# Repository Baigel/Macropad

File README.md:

This project is modified from Mattia Dal Ben's YamPad with a few changes that suit my specific needs (credit: https://github.com/mattdibi/yampad)

The Yampad project is an open-source, [QMK (Quantum Mechanical Keyboard Firmware)](https://github.com/qmk/qmk_firmware) powered, hot-swappable, RGB-backlighted, OLED featured, mechanical numpad.

## Primary Modifications from Original YamPad
 - Added 2 more switches for an array of 4x5 buttons (no more 2u keys)
 - Added spot for an IR sensor
 - Made the unused pins more accessible (added them as expansion pins on the side; with room for a decoupling capacitor)
 - Redid the PCB design (basically designed the PCB from scratch, used Mattia Dal Ben's design as a guide)
 - Different mounting holes (in hindsight, the Pro Micro may cover the holes in the top right - Oops!)

## YamPad Features:
- Cheap to build: the PCB can be manufactured for less than 1$ per piece.
- Easy to source components.
- Easy to build.
- Hot swappable keys using *Kailh PCB sockets*.
- Arduino Pro Micro powered.
- QMK compatible.
- RGB backlighting support (optional).
- OLED 0.91" screen (optional).
- Completely open-source.

## Bill of materials

| Qty | Item                                 | Notes                                     |
|-----|--------------------------------------|-------------------------------------------|
| 1   | Arduino Pro Micro (ATmega32u4)       | a.k.a. SparkFun Pro Micro                 |
| 20  | Cherry MX compatible switches        |                                           |
| 20  | SOD-123 1N4148/1N4148W diodes        |                                           |
| 20  | Kailh PCB sockets CPG151101S11       |                                           |
| 10  | WS2812B RGB LEDs                     |                                           |
| 10  | SMD 0805 100nF capacitors            |                                           |
| 1   | I2C 0.91" 128*32 OLED Display Module | The ones using SSD1306 driver IC over I2C |
| 1   | 6mm*6mm button switch                |                                           |
| 1   | YamPAD/Macropad PCB                  |                                           |
| 5   | M3 screws                            |                                           |

Note that I have included my personal shopping list (with links) in /Macropad/Bill_of_Materials.txt for reference

## Assembly guide

Not necessary to assemble in this order. More details can be found on the official YamPad repository (https://github.com/mattdibi/yampad).

1. Start with soldering the **WS2812 LEDs**. Start by applying solder to a pad, then heat it up while adding the component, finally solder the remaining pads.
2. Now add the **0805 100nF caps**. Use the same technique as before.
3. Add the **1N4148 diodes**.
4. Add the **CPG151101S11 Kailh PCB sockets**.
5. Add the **reset 6mm button switch**.
6. Add some electrical tape just to be sure.
7. Add the **Arduino Pro Micro** bottom side up.
8. Add the **OLED screen**
9. Move to the firmware section and you should be set!

## Firmware

For now the firmware is available through mattdibi's [QMK firmware repository fork](https://github.com/mattdibi/qmk_firmware/tree/yampad).

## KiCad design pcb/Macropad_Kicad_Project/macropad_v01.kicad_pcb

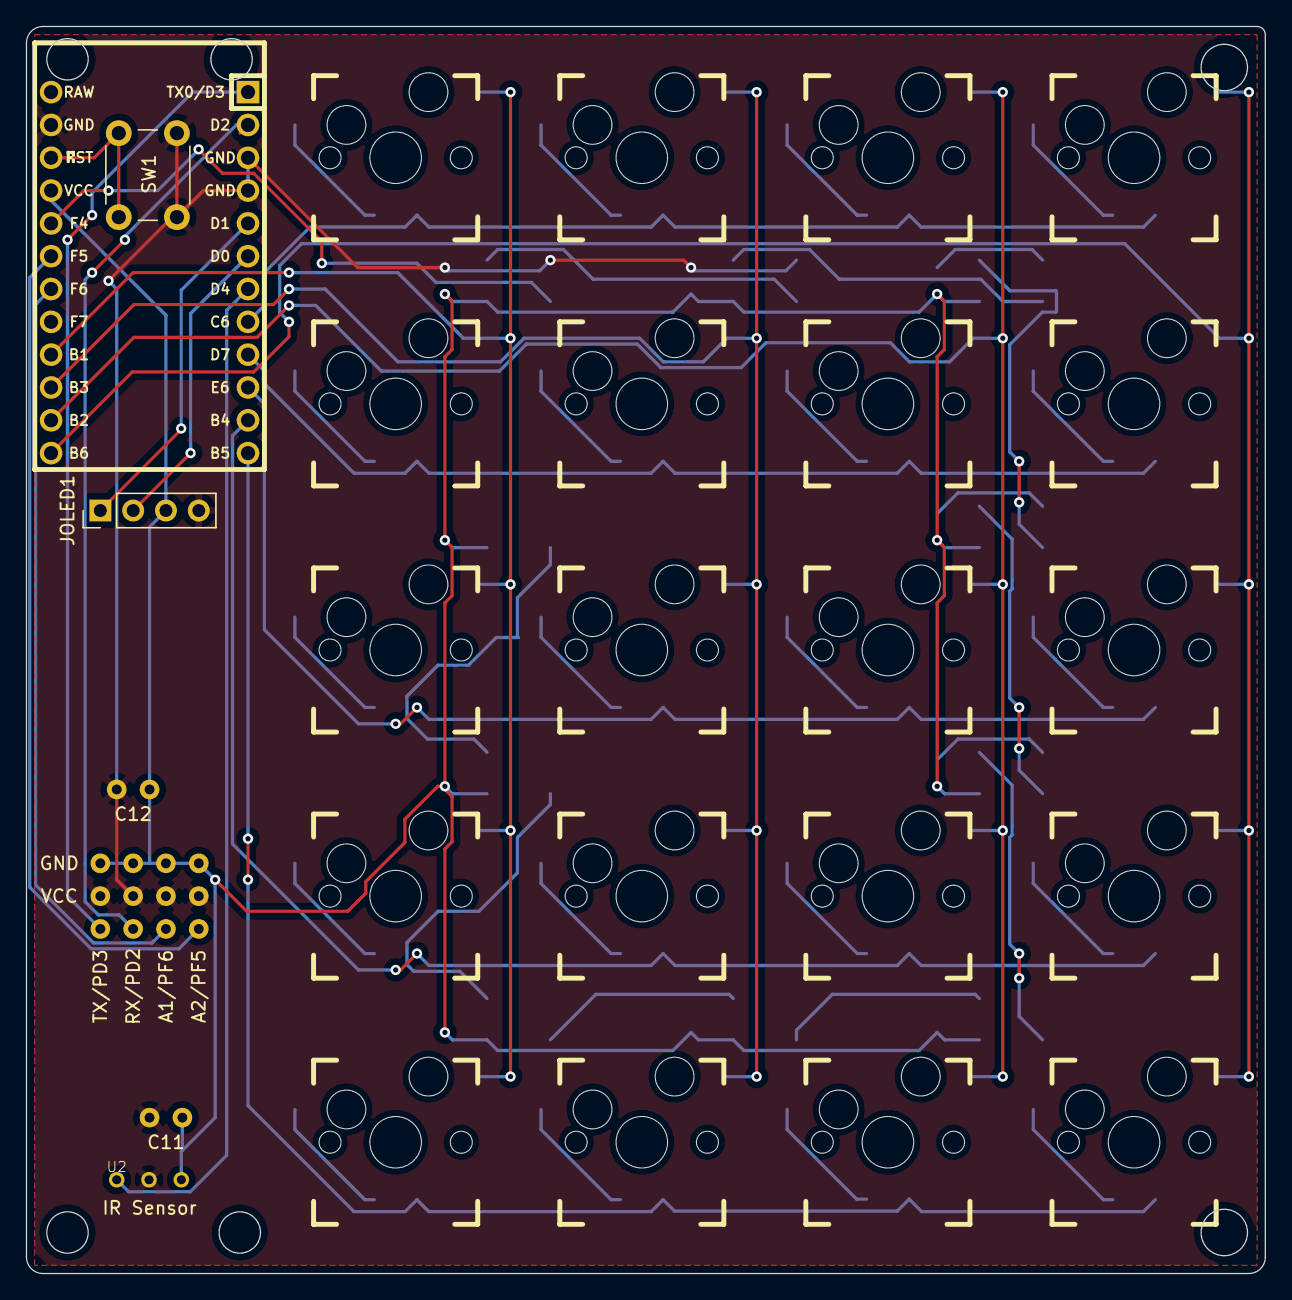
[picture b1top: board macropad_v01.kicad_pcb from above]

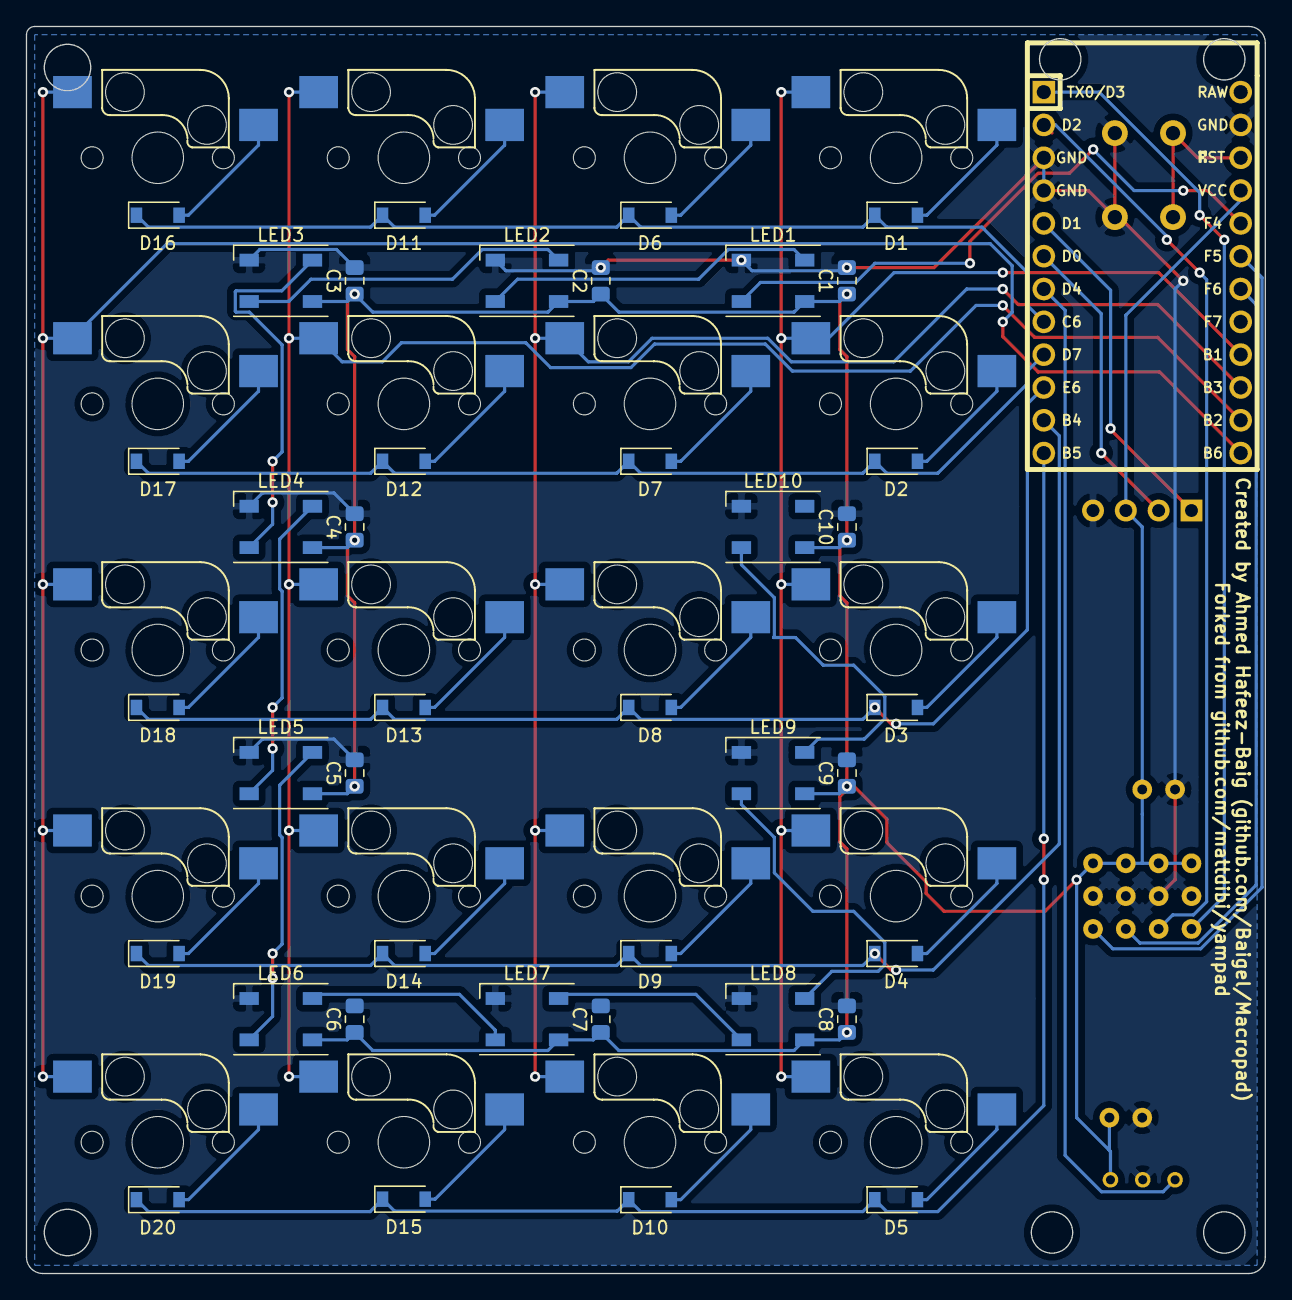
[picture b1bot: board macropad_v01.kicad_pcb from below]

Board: 2 copper layers, 95.9 x 96.5 mm, 67 parts (41 on the bottom side), 49 nets.

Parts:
C1, C2, C3, C4, C5, C6, C7, C8, C9, C10: 104; C_0805_2012Metric_Pad1.15x1.40mm_HandSolder
C11: macropad_v01-rescue_Symbols-Cache_Device_C-Symbol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; Capacitor-(100uF)
C12: Device_C-Symbols-Cache; Capacitor-(100uF)
D1, D2, D3, D4, D5, D6, D7, D8, D9, D10, D11, D12, D13, D14, D15, D16, D17, D18, D19, D20: D; D_SOD-123
J2: Expansion-Connector; Expansion-Pins
JOLED1: Conn_01x04; PinHeader_1x04_P2.54mm_Vertical
K1, K2, K3, K4, K5, K6, K7, K8, K9, K10, K11, K12, K13, K14, K15, K18, K19, K20: KEYSW; Kailh-PCB-Socket-1U-Cutout
K16, K17: KEYSW-canadian_parts-yampad_v2-rescue; Kailh-PCB-Socket-1U-Cutout
LED1, LED2, LED3, LED4, LED5, LED6, LED7, LED8, LED9, LED10: WS2812B; LED_WS2812B_PLCC4_5.0x5.0mm_P3.2mm
SW1: SW_Push; SW_PUSH_6mm
U1: ProMicro; ArduinoProMicro
U2: IR-Sensor; TSOP-382

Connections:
A1: J2.3, U1.18
A2: J2.4, U1.19
COL0: K1.1, K2.1, K3.1, K4.1, K5.1, U1.16
COL1: K6.1, K7.1, K8.1, K9.1, K10.1, U1.15
COL2: K11.1, K12.1, K13.1, K14.1, K15.1, U1.14
COL3: K16.1, K17.1, K18.1, K19.1, K20.1, U1.13
GND: C1.1, C2.1, C3.1, C4.1, C5.1, C6.1, C7.1, C8.1, C9.1, C10.1, C11.1, C12.1, J2.5, J2.6, J2.7, J2.8, JOLED1.4, LED1.3, LED2.3, LED3.3, LED4.3, LED5.3, LED6.3, LED7.3, LED8.3, LED9.3, LED10.3, SW1.1, U1.3, U1.4, U1.23, U2.GND
IR: U1.7, U2.OUT
LEDs: LED1.4, U1.20
unnamed: D1.2, K1.2
unnamed: D2.2, K2.2
unnamed: D3.2, K3.2
unnamed: D4.2, K4.2
unnamed: D5.2, K5.2
unnamed: D6.2, K6.2
unnamed: D7.2, K7.2
unnamed: D8.2, K8.2
unnamed: D9.2, K9.2
unnamed: D10.2, K10.2
unnamed: D11.2, K11.2
unnamed: D12.2, K12.2
unnamed: D13.2, K13.2
unnamed: D14.2, K14.2
unnamed: D15.2, K15.2
unnamed: D16.2, K16.2
unnamed: D17.2, K17.2
unnamed: D18.2, K18.2
unnamed: D19.2, K19.2
unnamed: D20.2, K20.2
unnamed: LED1.2, LED2.4
unnamed: LED2.2, LED3.4
unnamed: LED3.2, LED4.4
unnamed: LED4.2, LED5.4
unnamed: LED5.2, LED6.4
unnamed: LED6.2, LED7.4
unnamed: LED7.2, LED8.4
unnamed: LED8.2, LED9.4
unnamed: LED9.2, LED10.4
ROW0: D1.1, D6.1, D11.1, D16.1, U1.8
ROW1: D2.1, D7.1, D12.1, D17.1, U1.9
ROW2: D3.1, D8.1, D13.1, D18.1, U1.10
ROW3: D4.1, D9.1, D14.1, D19.1, U1.11
ROW4: D5.1, D10.1, D15.1, D20.1, U1.12
RST: SW1.2, U1.22
RX: J2.2, U1.2
SCL: JOLED1.2, U1.6
SDA: JOLED1.1, U1.5
TX: J2.1, U1.1
VCC: C1.2, C2.2, C3.2, C4.2, C5.2, C6.2, C7.2, C8.2, C9.2, C10.2, C11.2, C12.2, J2.9, J2.10, J2.11, J2.12, JOLED1.3, LED1.1, LED2.1, LED3.1, LED4.1, LED5.1, LED6.1, LED7.1, LED8.1, LED9.1, LED10.1, U1.21, U2.VS

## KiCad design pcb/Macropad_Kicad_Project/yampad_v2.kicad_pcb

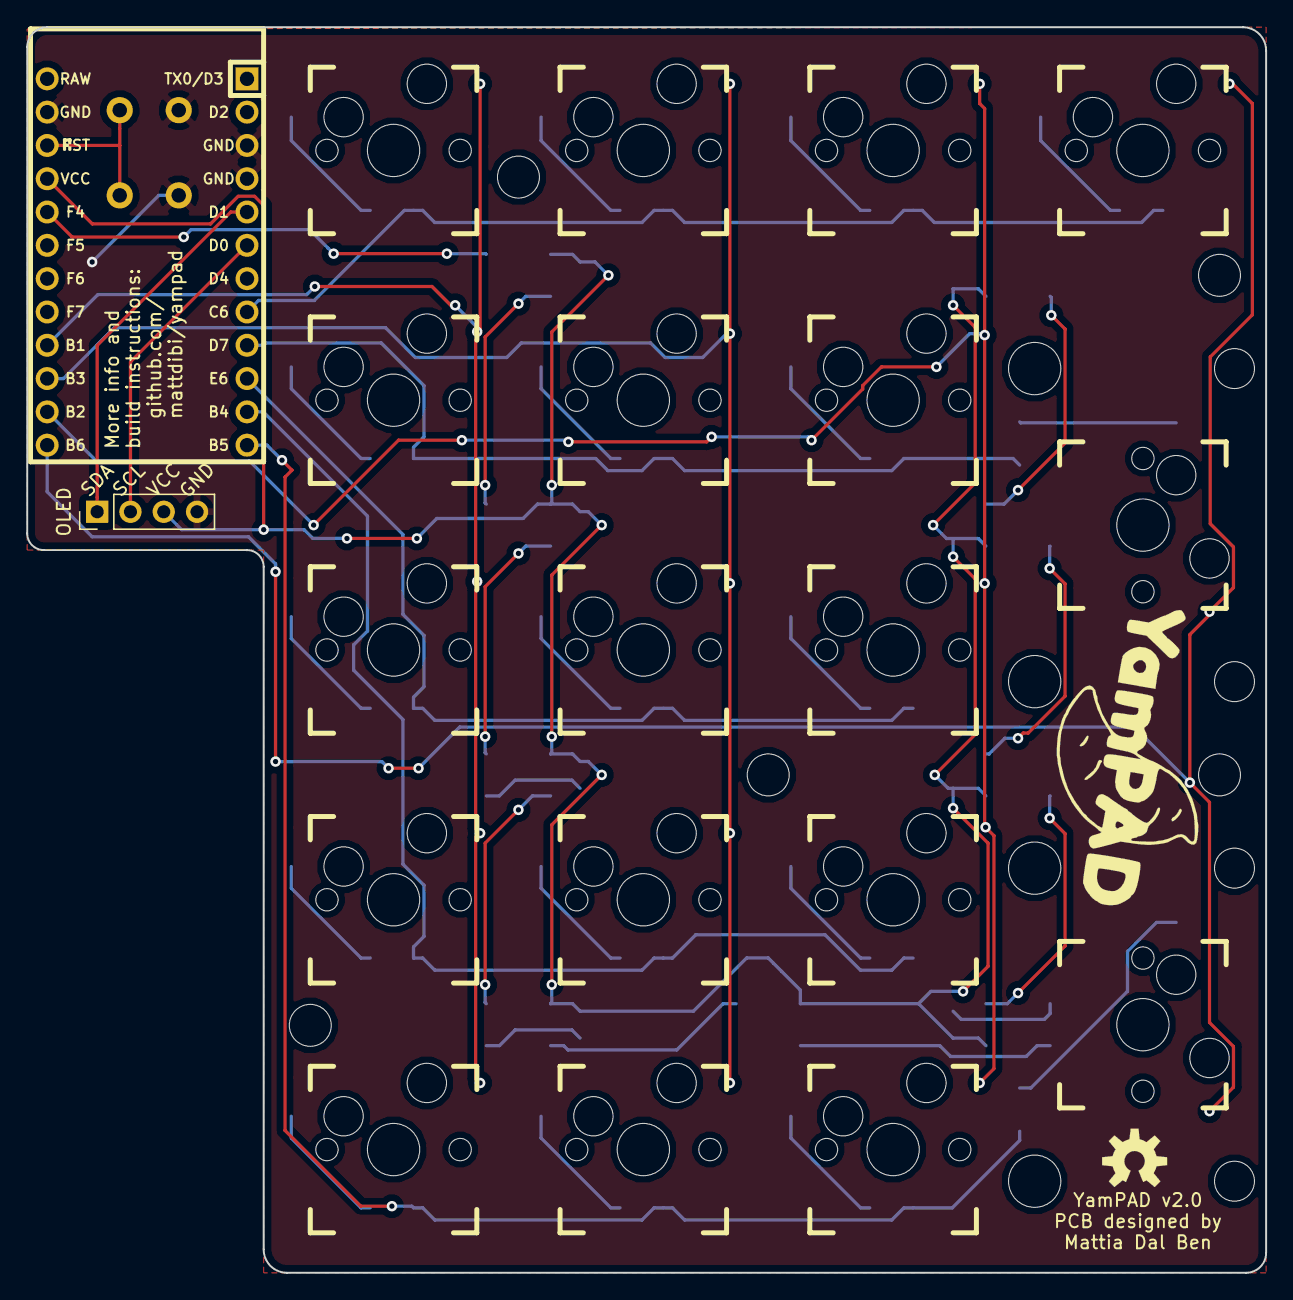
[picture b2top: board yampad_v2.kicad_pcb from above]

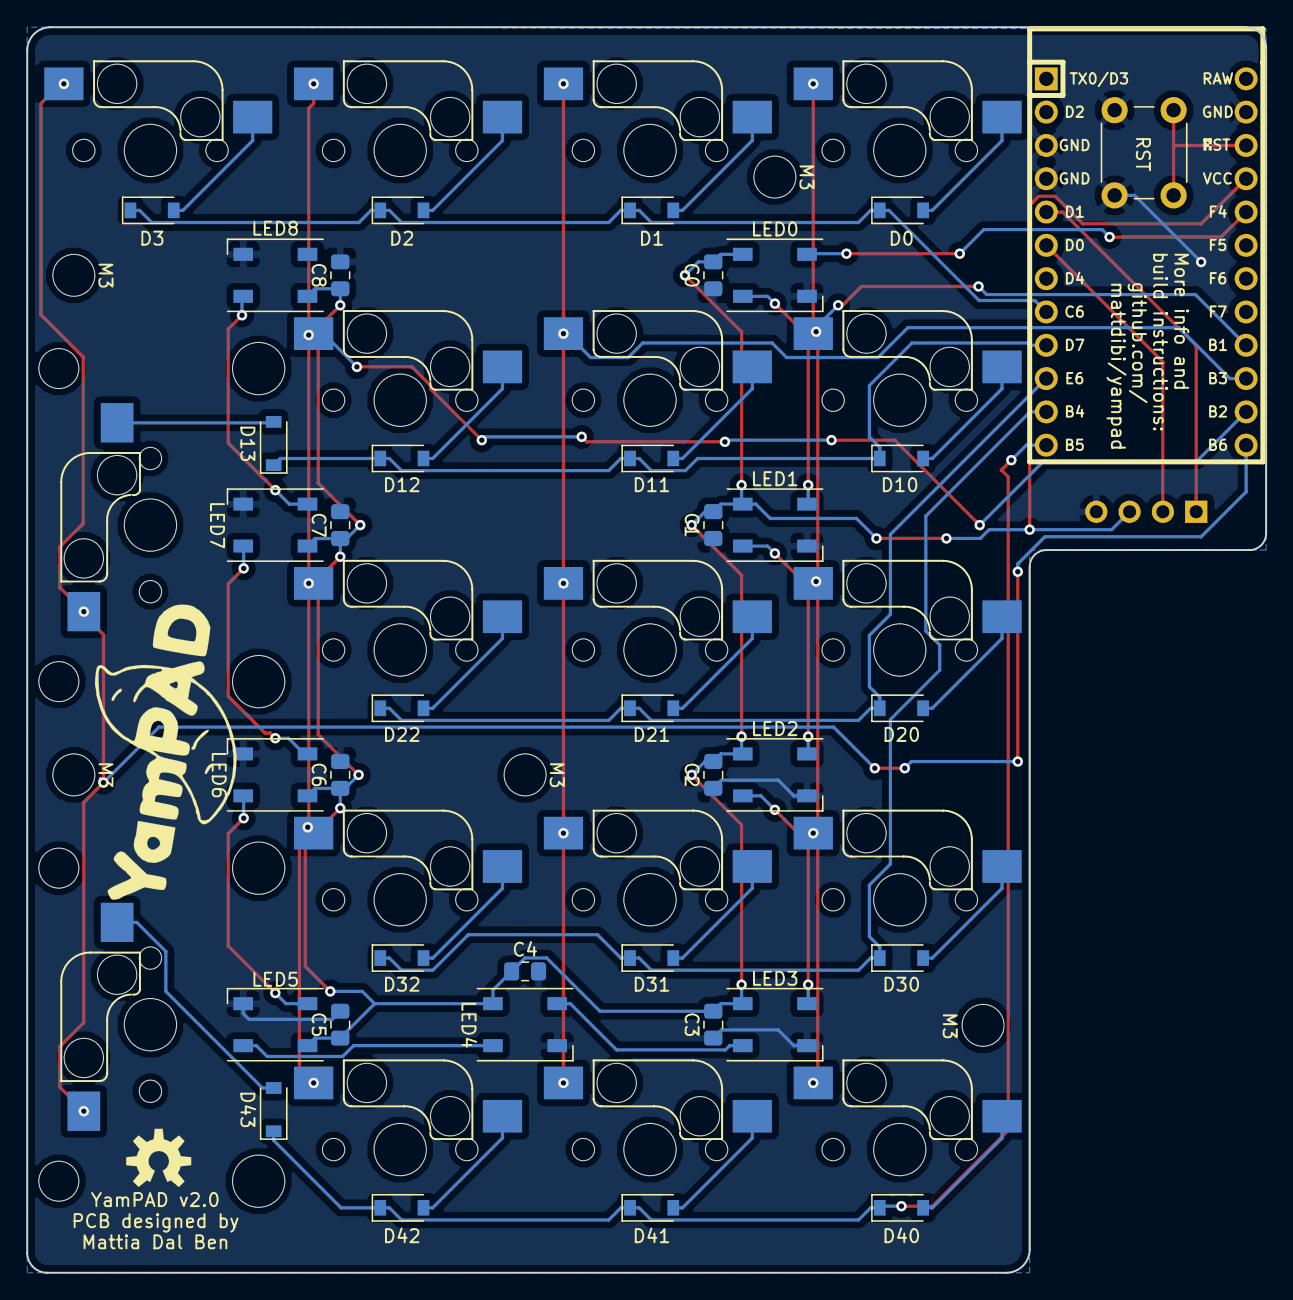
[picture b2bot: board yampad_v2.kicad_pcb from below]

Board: 2 copper layers, 94.5 x 95.0 mm, 62 parts (43 on the bottom side), 41 nets.

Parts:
C0, C1, C2, C3, C4, C5, C6, C7, C8: 104; C_0805_2012Metric_Pad1.15x1.40mm_HandSolder
D0, D1, D2, D3, D10, D11, D12, D13, D20, D21, D22, D30, D31, D32, D40, D41, D42, D43: D; D_SOD-123
K0, K1, K2, K3, K10, K11, K12, K20, K21, K22, K30, K31, K32, K40, K41, K42: KEYSW; Kailh-PCB-Socket-1U-Cutout
K13, K43: KEYSW; Kailh-PCB-Socket-2U
LED0, LED1, LED2, LED3, LED4, LED5, LED6, LED7, LED8: WS2812B; LED_WS2812B_PLCC4_5.0x5.0mm_P3.2mm
M3, M3#2, M3#3, M3#4, M3#5: MountingHole_3.2mm_M3
OLED: Conn_01x04; PinHeader_1x04_P2.54mm_Vertical
RST: SW_Push; SW_PUSH_6mm
U0: ProMicro; ArduinoProMicro

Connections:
COL0: K0.1, K10.1, K20.1, K30.1, K40.1, U0.16
COL1: K1.1, K11.1, K21.1, K31.1, K41.1, U0.15
COL2: K2.1, K12.1, K22.1, K32.1, K42.1, U0.14
COL3: K3.1, K13.1, K43.1, U0.13
GND: C0.1, C1.1, C2.1, C3.1, C4.1, C5.1, C6.1, C7.1, C8.1, LED0.3, LED1.3, LED2.3, LED3.3, LED4.3, LED5.3, LED6.3, LED7.3, LED8.3, OLED.4, RST.1, U0.3, U0.4, U0.23
LEDs: LED0.4, U0.20
unnamed: D0.2, K0.2
unnamed: D1.2, K1.2
unnamed: D2.2, K2.2
unnamed: D3.2, K3.2
unnamed: D10.2, K10.2
unnamed: D11.2, K11.2
unnamed: D12.2, K12.2
unnamed: D13.2, K13.2
unnamed: D20.2, K20.2
unnamed: D21.2, K21.2
unnamed: D22.2, K22.2
unnamed: D30.2, K30.2
unnamed: D31.2, K31.2
unnamed: D32.2, K32.2
unnamed: D40.2, K40.2
unnamed: D41.2, K41.2
unnamed: D42.2, K42.2
unnamed: D43.2, K43.2
unnamed: LED0.2, LED1.4
unnamed: LED1.2, LED2.4
unnamed: LED2.2, LED3.4
unnamed: LED3.2, LED4.4
unnamed: LED4.2, LED5.4
unnamed: LED5.2, LED6.4
unnamed: LED6.2, LED7.4
unnamed: LED7.2, LED8.4
ROW0: D0.1, D1.1, D2.1, D3.1, U0.8
ROW1: D10.1, D11.1, D12.1, D13.1, U0.9
ROW2: D20.1, D21.1, D22.1, U0.10
ROW3: D30.1, D31.1, D32.1, U0.11
ROW4: D40.1, D41.1, D42.1, D43.1, U0.12
RST: RST.2, U0.22
SCL: OLED.2, U0.6
SDA: OLED.1, U0.5
VCC: C0.2, C1.2, C2.2, C3.2, C4.2, C5.2, C6.2, C7.2, C8.2, LED0.1, LED1.1, LED2.1, LED3.1, LED4.1, LED5.1, LED6.1, LED7.1, LED8.1, OLED.3, U0.21

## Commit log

2020-06-30 Update README.md
    Took out a lot of the stuff that was in the original YamPad repo (just to cut down on stuff that I don't need) - if you want more details go visit the original repo.
2020-07-14 Working on PCB
    Still to do:
    - Add decoupling resistor to IR sensor
    - Add decoupling resistor place for extra pins
    - Complete PCB (still laying out things)
    - Do all the wire runs for the PCB
2020-07-15 PCB DONE!!!
    (i think)
2020-07-15 Generated Gerber
    probs should redo the way jlcpcb wants it done
2020-07-17 commited gerber files (the correct ones needed for jlcpcb)
2020-07-20 Added my personal shopping list that I used when creating this project
2020-07-20 no spaces :((((
2020-07-20 Update README.md
    finished the PCB design, so I have just polished the readme a bit
2020-10-30 Fixed number of items in BOM to better represent macropad
2020-10-30 Spelling mistake in README.md
